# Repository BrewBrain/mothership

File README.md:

---
description: An overview of your brews and more
---

# Dashboard

## The dashboard

Voici un exemple de tableau de bord:

```bash

```

{% hint style="info" %}
 Super-powers are granted randomly so please submit an issue if you're not happy with yours.
{% endhint %}

Once you're strong enough, save the world:

{% code title="hello.sh" %}
```bash
# Ain't no code for that yet, sorry
echo 'You got to trust me on this, I saved the world'
```
{% endcode %}

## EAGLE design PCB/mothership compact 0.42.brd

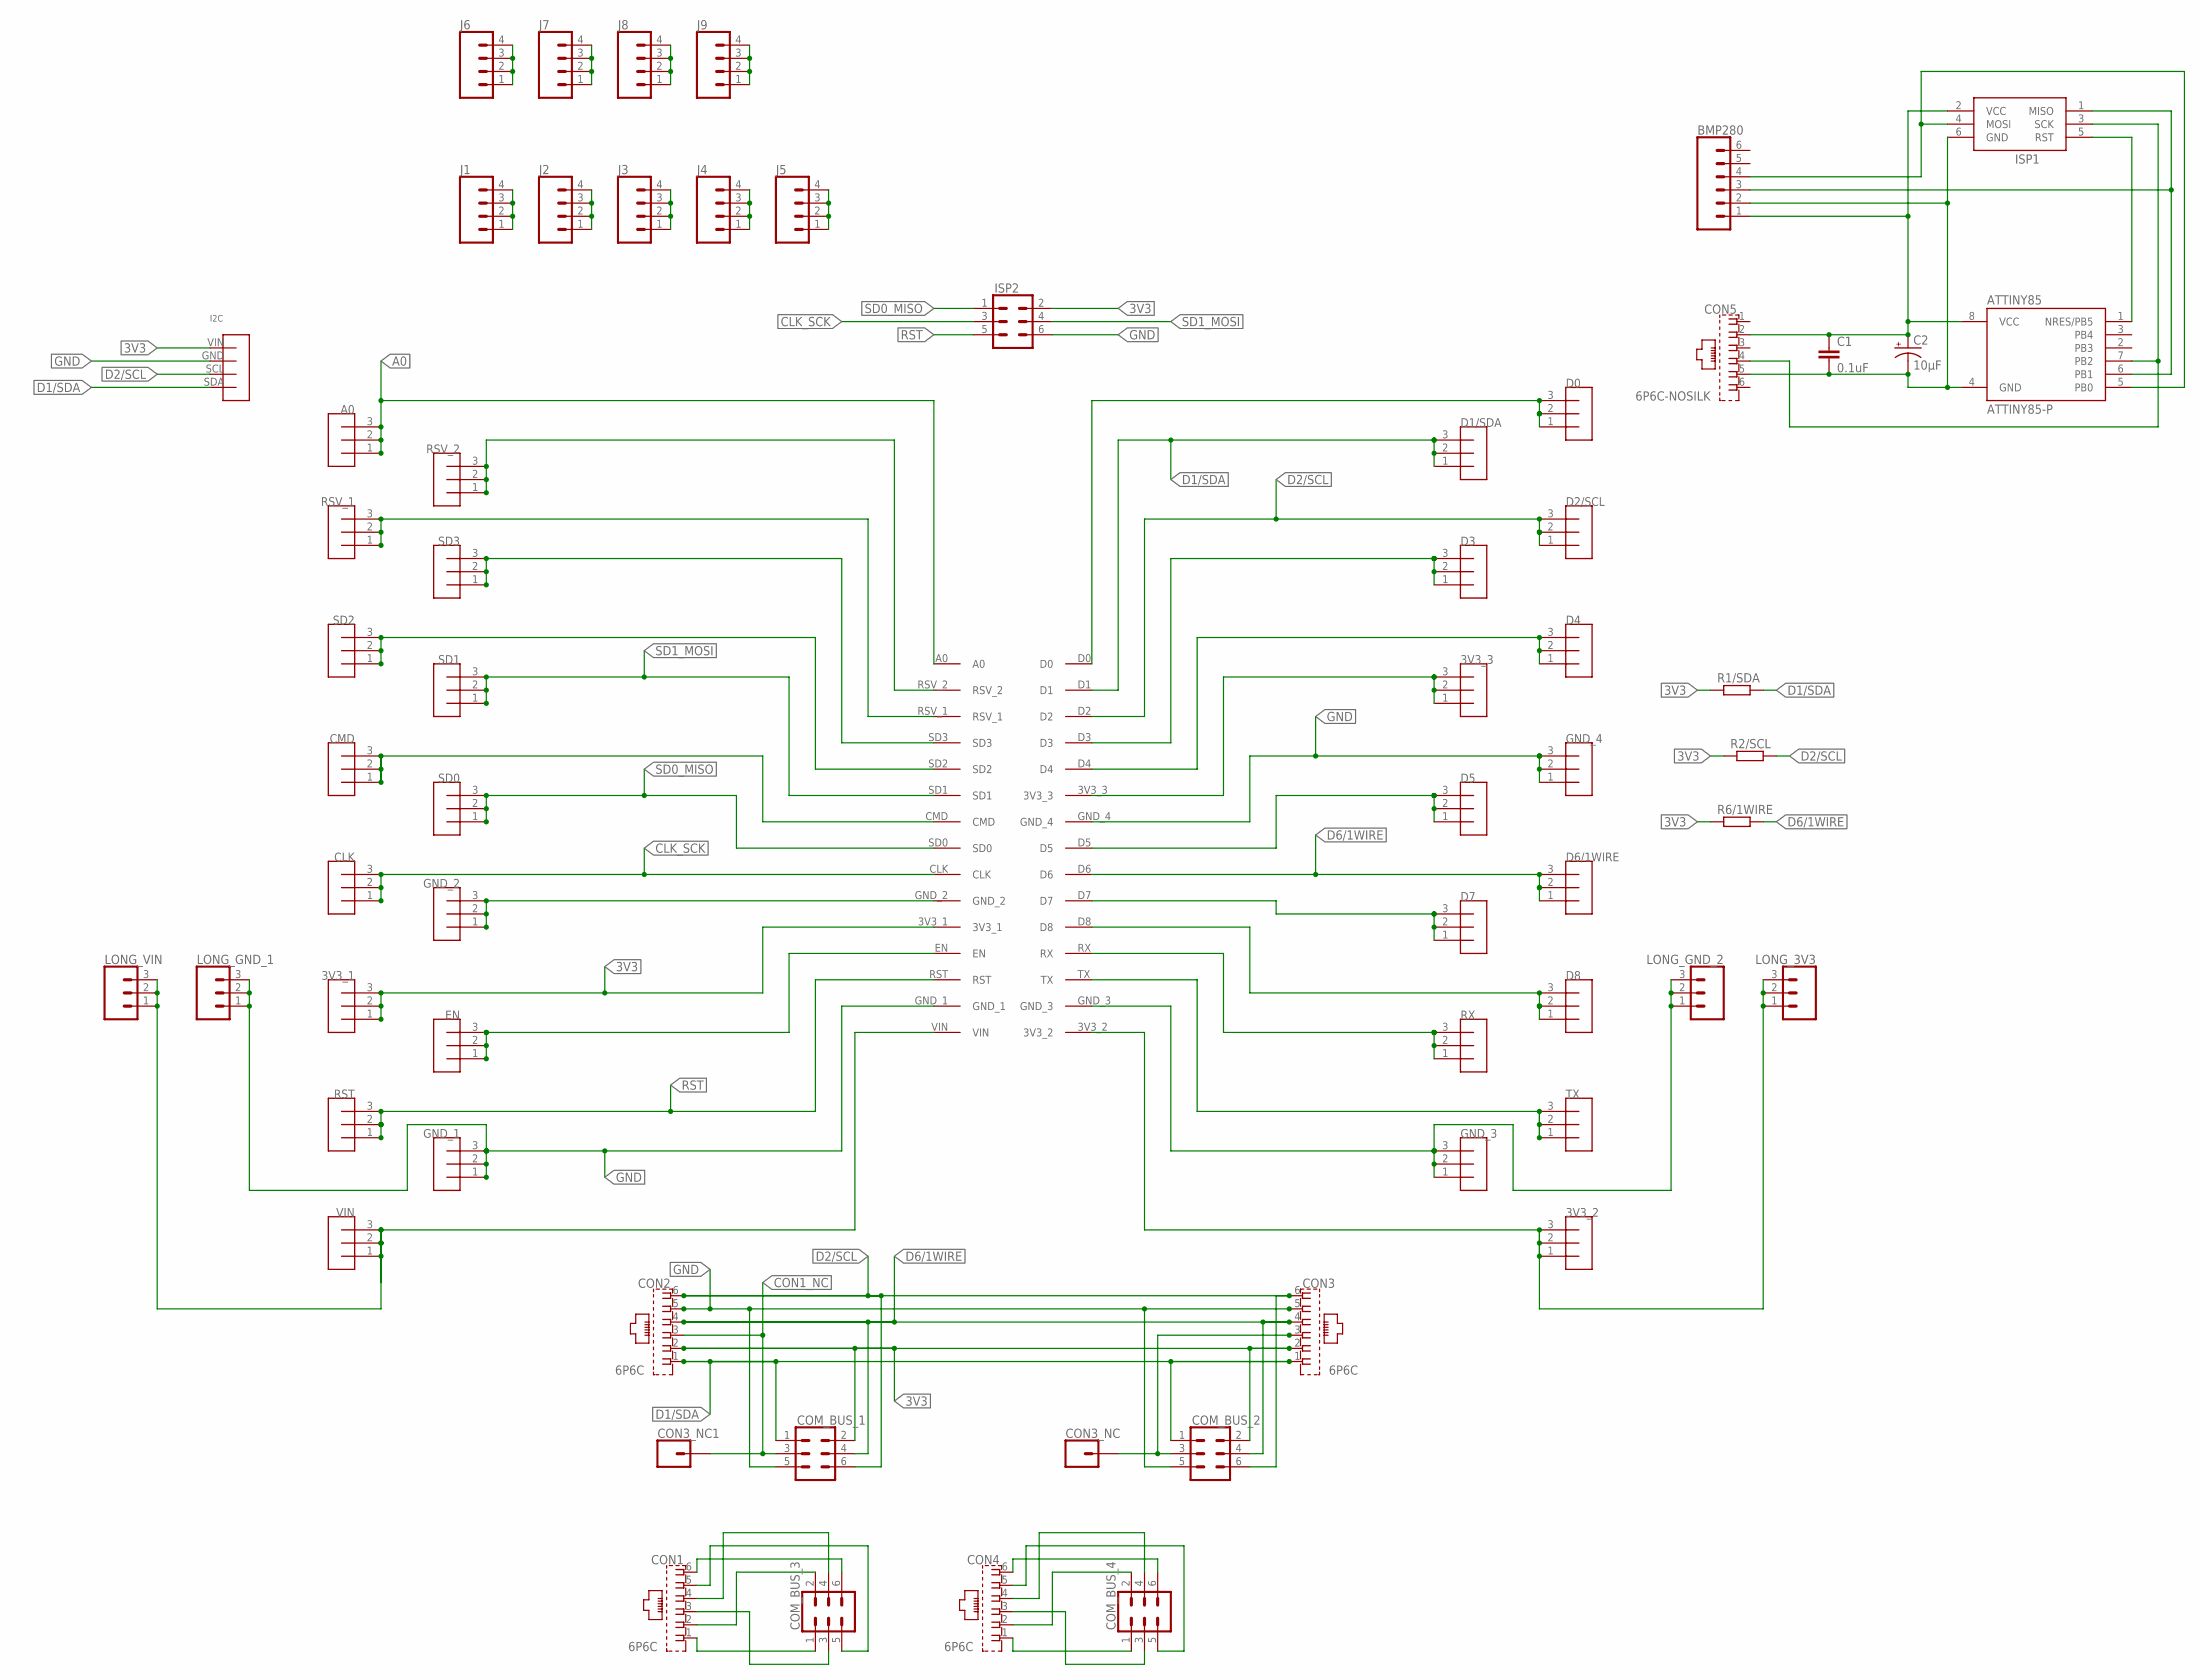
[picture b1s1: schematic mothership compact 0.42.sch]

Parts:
3V3_1, 3V3_2, 3V3_3: JUMPERS; 3PIN
A0: JUMPERS; 3PIN
ATTINY85: ATTINY85-P; PDIP08_300MIL
BMP280: CONN_06NO_SILK_NO_POP; 1X06_NO_SILK
C1: 0.1uF; C050-045X075
C2: 10µF; E2,5-5
CLK: JUMPERS; 3PIN
CMD: JUMPERS; 3PIN
COM_BUS_1, COM_BUS_2, COM_BUS_3, COM_BUS_4: CONN_03X2NO_SILK; 2X3-NS
CON1, CON2, CON3, CON4: 6P6C; RJ11-6P6C-NOSHIELD
CON3_NC, CON3_NC1: CONN_01PTH_NO_SILK_YES_STOP; 1X01_NO_SILK
CON5: 6P6C-NOSILK; RJ11-6P6C-NOSHIELD-NOSILK
D0, D1/SDA, D2/SCL, D3, D4, D5, D6/1WIRE, D7, D8: JUMPERS; 3PIN
EN: JUMPERS; 3PIN
GND_1, GND_2, GND_3, GND_4: JUMPERS; 3PIN
ISP1: AVRISP-6; AVRISP
ISP2: CONN_03X2NO_SILK; 2X3-NS
J1, J2, J3, J4, J5, J6, J7, J8, J9: CONN_041X04_NO_SILK; 1X04_NO_SILK
LONG_3V3: CONN_03; 1X03
LONG_GND_1, LONG_GND_2: CONN_03; 1X03
LONG_VIN: CONN_03; 1X03
R1/SDA, R2/SCL, R6/1WIRE: R-EU_0207/10; 0207/10
RST: JUMPERS; 3PIN
RSV_1, RSV_2: JUMPERS; 3PIN
RX: JUMPERS; 3PIN
SD0, SD1, SD2, SD3: JUMPERS; 3PIN
TX: JUMPERS; 3PIN
U$1: NODEMCU
U$2: I2CJUMPER; 4PIN,NAMED
VIN: JUMPERS; 3PIN

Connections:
3V3: 3V3_1.1, 3V3_1.2, 3V3_1.3, 3V3_2.1, 3V3_2.2, 3V3_2.3, 3V3_3.1, 3V3_3.2, 3V3_3.3, COM_BUS_1.2, COM_BUS_2.2, CON2.2 (5), CON3.2 (5), ISP2.2, LONG_3V3.1, LONG_3V3.2, LONG_3V3.3, R1/SDA.1, R2/SCL.1, R6/1WIRE.1, U$1.3V3_1, U$1.3V3_2, U$1.3V3_3, U$2.VIN
A0: A0.1, A0.2, A0.3, U$1.A0
ATT85_VCC: ATTINY85.8 (VCC), BMP280.1, C1.1, C2.+, CON5.2, ISP1.2 (VCC)
ATT_GND: ATTINY85.4 (GND), BMP280.2, C1.2, C2.-, CON5.5, ISP1.6 (GND)
CLK_SCK: CLK.1, CLK.2, CLK.3, ISP2.3, U$1.CLK
CON1_NC: COM_BUS_1.3, CON2.3 (4), CON3_NC1.1
CON3_NC: COM_BUS_2.3, CON3.3 (4), CON3_NC.1
D1/SDA: COM_BUS_1.1, COM_BUS_2.1, CON2.1 (6), CON3.1 (6), D1/SDA.1, D1/SDA.2, D1/SDA.3, R1/SDA.2, U$1.D1, U$2.SDA
D2/SCL: COM_BUS_1.6, COM_BUS_2.6, CON2.6 (1), CON3.6 (1), D2/SCL.1, D2/SCL.2, D2/SCL.3, R2/SCL.2, U$1.D2, U$2.SCL
D6/1WIRE: COM_BUS_1.4, COM_BUS_2.4, CON2.4 (3), CON3.4 (3), D6/1WIRE.1, D6/1WIRE.2, D6/1WIRE.3, R6/1WIRE.2, U$1.D6
GND: COM_BUS_1.5, COM_BUS_2.5, CON2.5 (2), CON3.5 (2), GND_1.1, GND_1.2, GND_1.3, GND_2.1, GND_2.2, GND_2.3, GND_3.1, GND_3.2, GND_3.3, GND_4.1, GND_4.2, GND_4.3, ISP2.6, LONG_GND_1.1, LONG_GND_1.2, LONG_GND_1.3, LONG_GND_2.1, LONG_GND_2.2, LONG_GND_2.3, U$1.GND_1, U$1.GND_2, U$1.GND_3, U$1.GND_4, U$2.GND
unnamed: EN.1, EN.2, EN.3, U$1.EN
unnamed: D0.1, D0.2, D0.3, U$1.D0
unnamed: SD3.1, SD3.2, SD3.3, U$1.SD3
unnamed: J1.1, J1.2, J1.3, J1.4
unnamed: RSV_1.1, RSV_1.2, RSV_1.3, U$1.RSV_1
unnamed: SD2.1, SD2.2, SD2.3, U$1.SD2
unnamed: RSV_2.1, RSV_2.2, RSV_2.3, U$1.RSV_2
unnamed: CMD.1, CMD.2, CMD.3, U$1.CMD
unnamed: J2.1, J2.2, J2.3, J2.4
unnamed: J3.1, J3.2, J3.3, J3.4
unnamed: J4.1, J4.2, J4.3, J4.4
unnamed: J5.1, J5.2, J5.3, J5.4
unnamed: J6.1, J6.2, J6.3, J6.4
unnamed: J7.1, J7.2, J7.3, J7.4
unnamed: J8.1, J8.2, J8.3, J8.4
unnamed: J9.1, J9.2, J9.3, J9.4
unnamed: D4.1, D4.2, D4.3, U$1.D4
unnamed: COM_BUS_3.1, CON1.1 (6)
unnamed: D8.1, D8.2, D8.3, U$1.D8
unnamed: TX.1, TX.2, TX.3, U$1.TX
unnamed: COM_BUS_3.6, CON1.6 (1)
unnamed: COM_BUS_3.5, CON1.5 (2)
unnamed: RX.1, RX.2, RX.3, U$1.RX
unnamed: D7.1, D7.2, D7.3, U$1.D7
unnamed: D5.1, D5.2, D5.3, U$1.D5
unnamed: COM_BUS_3.4, CON1.4 (3)
unnamed: D3.1, D3.2, D3.3, U$1.D3
unnamed: COM_BUS_3.2, CON1.2 (5)
unnamed: COM_BUS_3.3, CON1.3 (4)
unnamed: COM_BUS_4.1, CON4.1 (6)
unnamed: COM_BUS_4.6, CON4.6 (1)
unnamed: COM_BUS_4.5, CON4.5 (2)
unnamed: COM_BUS_4.4, CON4.4 (3)
unnamed: COM_BUS_4.2, CON4.2 (5)
unnamed: COM_BUS_4.3, CON4.3 (4)
PB0: ATTINY85.5 (PB0), BMP280.4, ISP1.4 (MOSI)
PB1: ATTINY85.6 (PB1), BMP280.3, ISP1.1 (MISO)
PB2: ATTINY85.7 (PB2), CON5.4, ISP1.3 (SCK)
PB5: ATTINY85.1 (NRES/PB5), ISP1.5 (RST)
RST: ISP2.5, RST.1, RST.2, RST.3, U$1.RST
SD0_MISO: ISP2.1, SD0.1, SD0.2, SD0.3, U$1.SD0
SD1_MOSI: ISP2.4, SD1.1, SD1.2, SD1.3, U$1.SD1
VIN: LONG_VIN.1, LONG_VIN.2, LONG_VIN.3, U$1.VIN, VIN.1, VIN.2, VIN.3

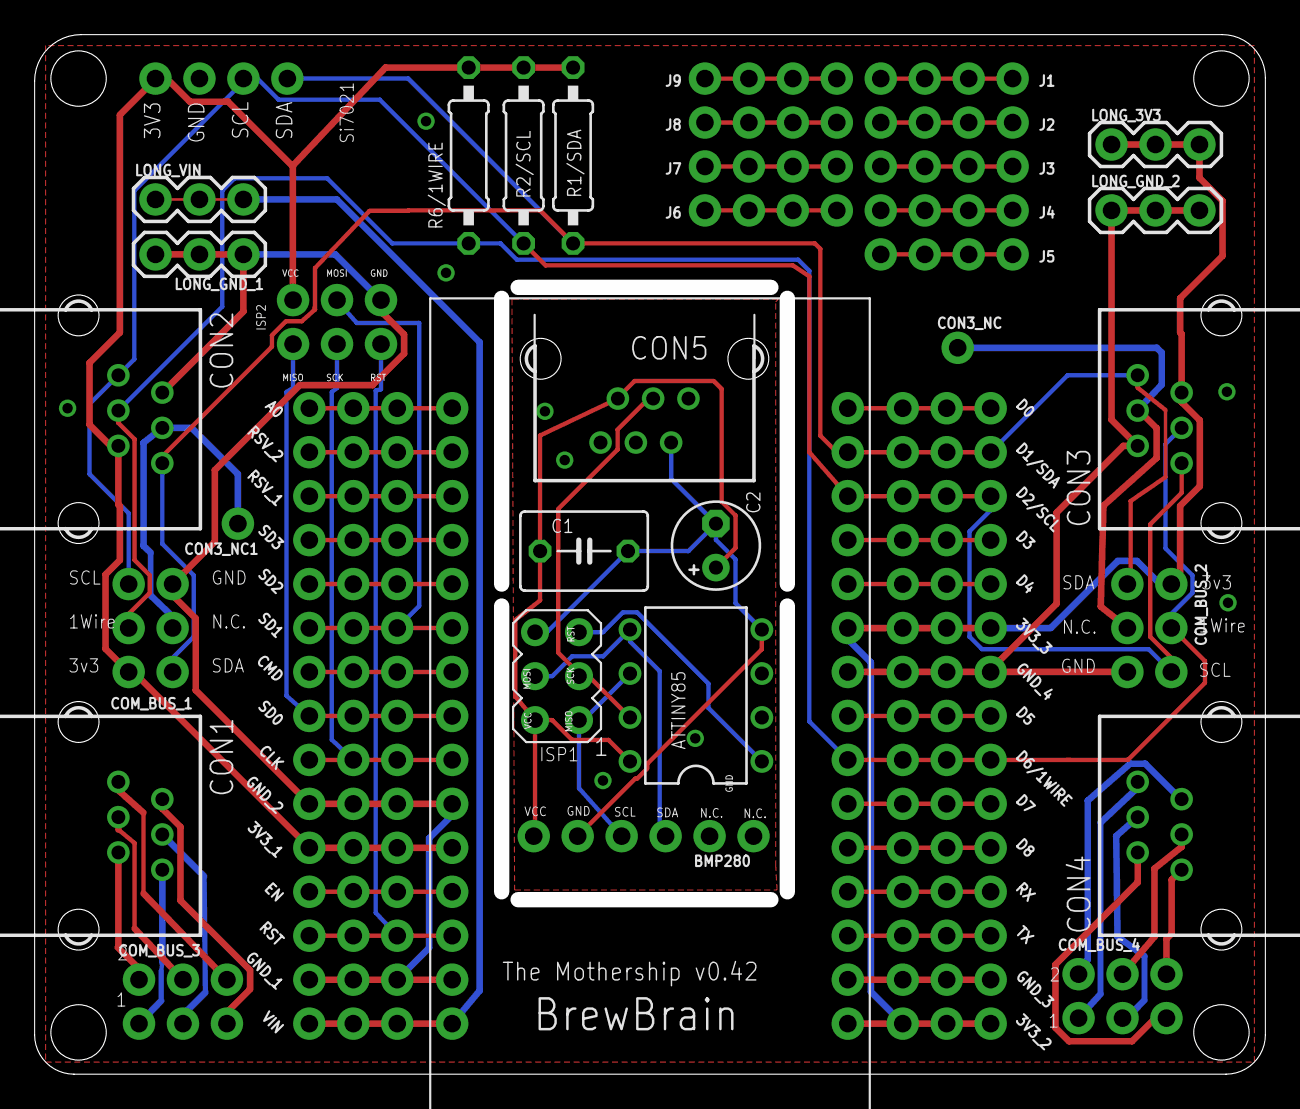
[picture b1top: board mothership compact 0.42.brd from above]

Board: 2 copper layers, 70.2 x 59.2 mm, 65 parts (0 on the bottom side), 54 nets.

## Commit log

2017-11-04 initial checkin of motherhip firmware
2017-11-04 initial checkin of PCB drawings
2017-11-04 initial checkin of housing
2017-11-04 Create LICENSE
2017-11-04 Update LICENSE
2021-03-25 GitBook: [master] 2 pages and 3 assets modified
2021-03-25 GitBook: [french] 5 pages and 3 assets modified

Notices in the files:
parts and their libraries:
SparkFun-Connectors: Licensing: Creative Commons ShareAlike 4.0 International - https://creativecommons.org/licenses/by-sa/4.0
